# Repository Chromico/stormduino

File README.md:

# Stormduino Rev 2.2
An open source arduino uno clone designed in KiCad in collaboration with tecknologg and cyberstorm.mu .The board uses the CH340C as the USB to serial converter and an Atmega328p (DIP) as the microcontroller. The board design and schematic is open source so do whatever you wish with it :)

My website: https://tecknologg.website

Blog post: https://tecknologg.website/2020/02/02/stormduino-the-arduino-compatible-board-made-in-kicad/

# Front 

# Back

# Assembled board

# Features

# Documentation
You can get the official documentation for stormduino here: https://github.com/Chromico/stormduino/blob/master/documentation.pdf

# Certification
As from 2020 Stormduino has the open source hardware certfication to show you that Stormduino is truly open source hardware.

# Contact

Need to contact me ? Just send me an email at nathan@tecknologg.website or tecknologg@gmail.com

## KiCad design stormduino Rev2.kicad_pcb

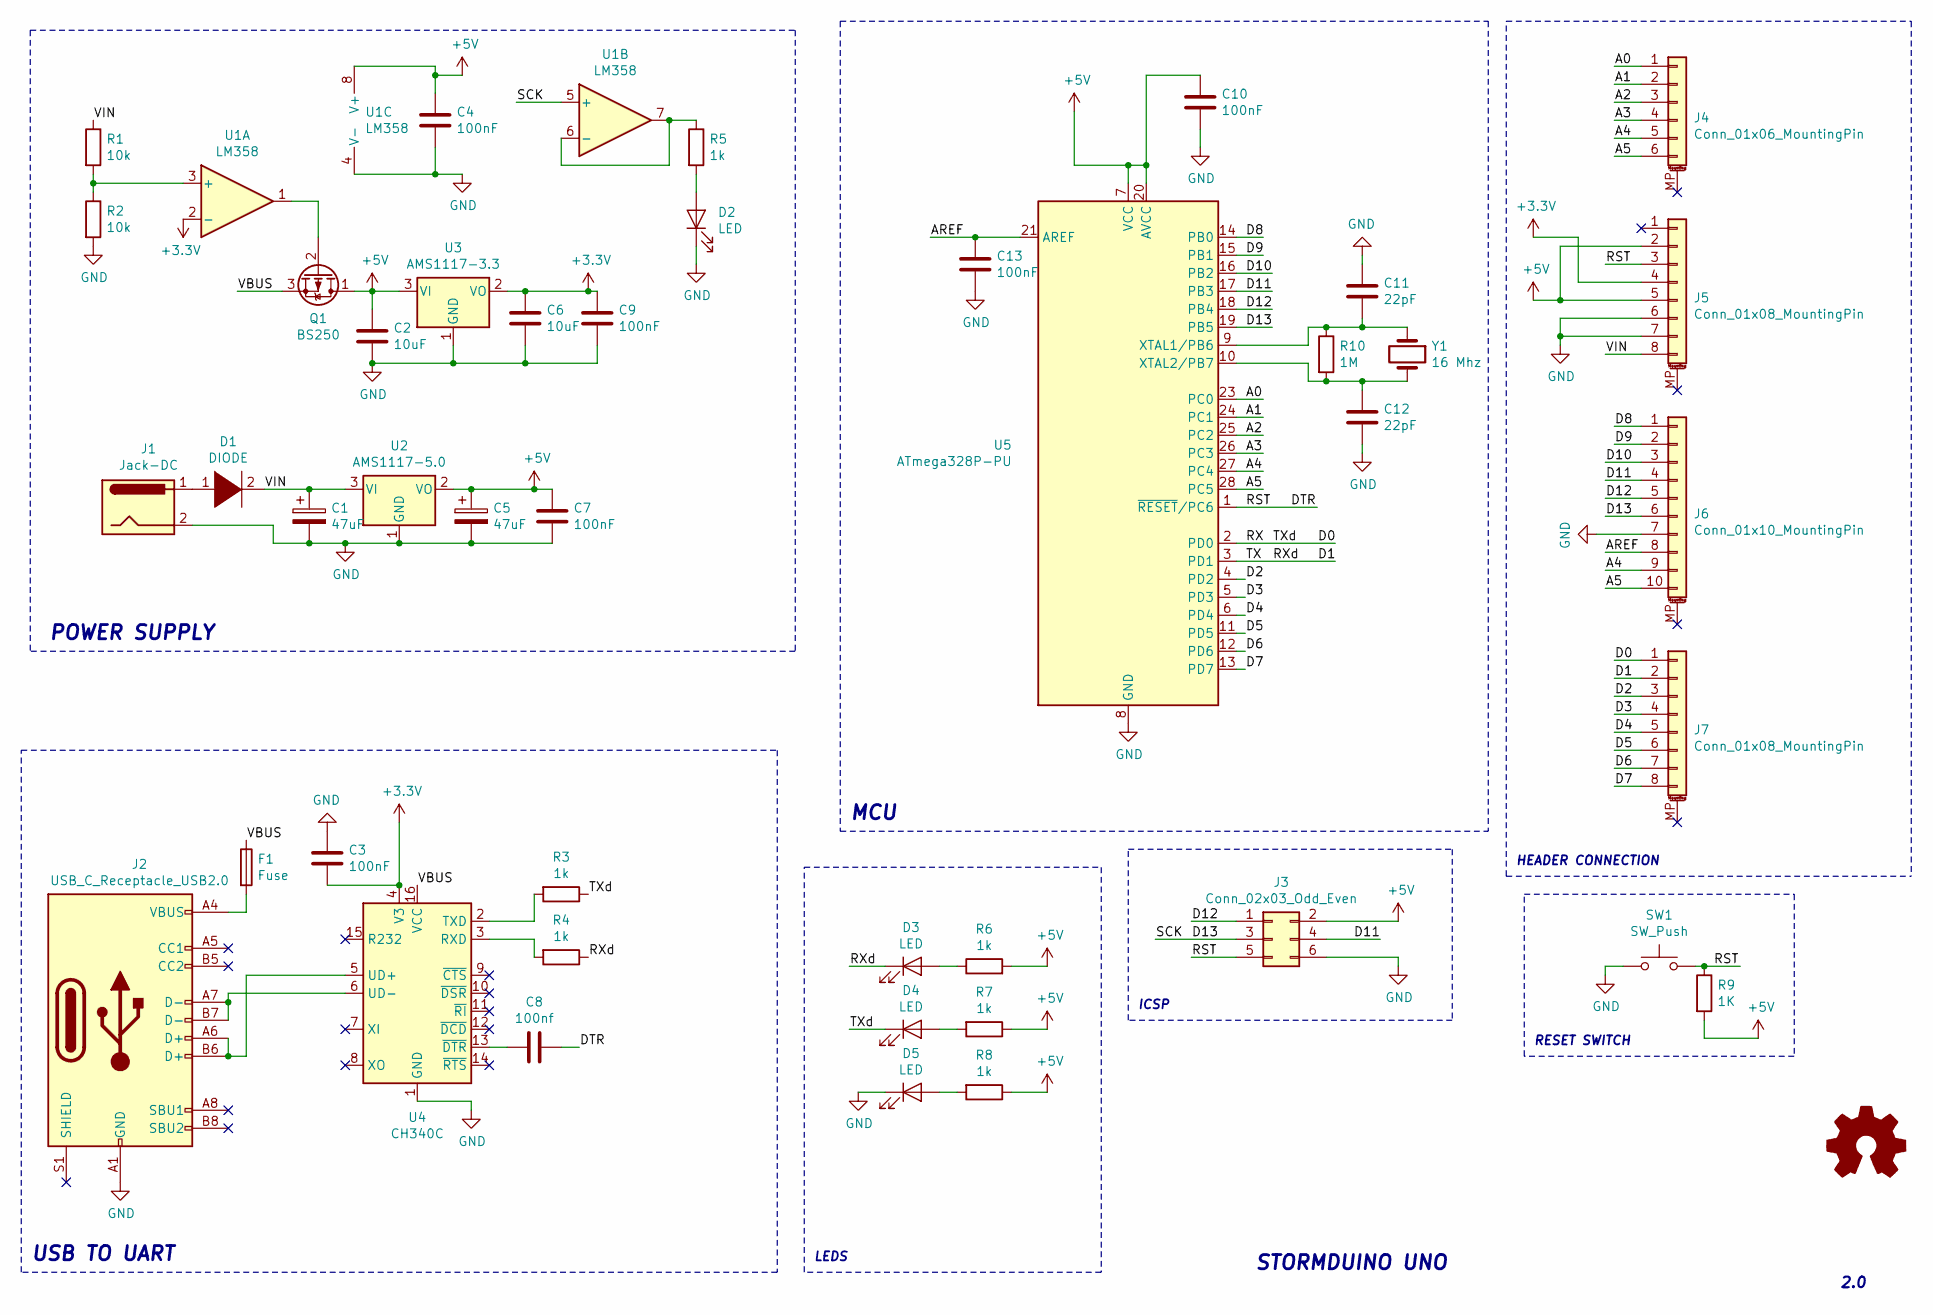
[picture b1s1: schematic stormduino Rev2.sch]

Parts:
C1, C5: 47uF
C2, C6: 10uF
C3, C4, C7, C9, C10, C13: 100nF
C8: 100nf
C11, C12: 22pF
D1: DIODE
D2, D3, D4, D5: LED
F1: Fuse
J1: Jack-DC
J2: USB_C_Receptacle_USB2.0
J3: Conn_02x03_Odd_Even
J4: Conn_01x06_MountingPin
J5, J7: Conn_01x08_MountingPin
J6: Conn_01x10_MountingPin
Q1: BS250; TO-92_Inline
R1, R2: 10k
R3, R4, R5, R6, R7, R8: 1k
R9: 1K
R10: 1M
SW1: SW_Push
U1: LM358
U2: AMS1117-5.0; SOT-223-3_TabPin2
U3: AMS1117-3.3; SOT-223-3_TabPin2
U4: CH340C; SOIC-16_3.9x9.9mm_P1.27mm
U5: ATmega328P-PU; DIP-28_W7.62mm
Y1: 16 Mhz

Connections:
+3V3: C3.2, C6.1, C9.1, J5.4, U1.2 (-), U3.2 (VO), U4.4 (V3)
/A0: J4.1, U5.23 (PC0)
/A1: J4.2, U5.24 (PC1)
/A2: J4.3, U5.25 (PC2)
/A3: J4.4, U5.26 (PC3)
/A4: J4.5, J6.9, U5.27 (PC4)
/A5: J4.6, J6.10, U5.28 (PC5)
/AREF: C13.1, J6.8, U5.21 (AREF)
/CTS: U4.9 (~CTS); also elsewhere on the board
/D0: D4.1 (K), J7.1, R3.1, U5.2 (PD0); also elsewhere on the board
/D1: D3.1 (K), J7.2, R4.1, U5.3 (PD1); also elsewhere on the board
/D2: J7.3, U5.4 (PD2)
/D3: J7.4, U5.5 (PD3)
/D4: J7.5, U5.6 (PD4)
/D5: J7.6, U5.11 (PD5)
/D6: J7.7, U5.12 (PD6)
/D7: J7.8, U5.13 (PD7)
/D8: J6.1, U5.14 (PB0)
/D9: J6.2, U5.15 (PB1)
/D10: J6.3, U5.16 (PB2)
/D11: J3.4, J6.4, U5.17 (PB3)
/D12: J3.1, J6.5, U5.18 (PB4)
/D13: J3.3, J6.6, U1.5 (+), U5.19 (PB5)
/DCD: U4.12 (~DCD); also elsewhere on the board
/DSR: U4.10 (~DSR); also elsewhere on the board
/DTR: C8.1, J3.5, J5.3, R9.1, SW1.2, U5.1 (~RESET~/PC6)
/R232: U4.15 (R232); also elsewhere on the board
/RI: U4.11 (~RI); also elsewhere on the board
/RTS: U4.14 (~RTS); also elsewhere on the board
/VBUS: F1.1, Q1.3 (S), U4.16 (VCC); also elsewhere on the board
/VIN: C1.1, D1.2 (A), J5.8, R1.1, U2.3 (VI)
GND: C1.2, C2.2, C3.1, C4.2, C5.2, C6.2, C7.2, C9.2, C10.2, C11.1, C12.2, C13.2, D2.1 (K), D5.1 (K), J1.2, J2.A1 (GND), J2.A12 (GND), J2.B1 (GND), J2.B12 (GND), J3.6, J5.6, J5.7, J6.7, R2.2, SW1.1, U1.4 (V-), U2.1 (GND), U3.1 (GND), U4.1 (GND), U5.8 (GND), U5.22 (GND); also elsewhere on the board
unnamed: C8.2, U4.13 (~DTR)
unnamed: C11.2, R10.1, U5.9 (XTAL1/PB6), Y1.1
unnamed: C12.1, R10.2, U5.10 (XTAL2/PB7), Y1.2
unnamed: D1.1 (K), J1.1
unnamed: D2.2 (A), R5.2
unnamed: D3.2 (A), R6.1
unnamed: D4.2 (A), R7.2
unnamed: D5.2 (A), R8.2
unnamed: F1.2, J2.A4 (VBUS), J2.A9 (VBUS), J2.B4 (VBUS), J2.B9 (VBUS)
unnamed: J2.A6 (D+), J2.B6 (D+), U4.5 (UD+)
unnamed: J2.A7 (D-), J2.B7 (D-), U4.6 (UD-)
unnamed: R1.2, R2.1, U1.3 (+)
unnamed: R3.2, U4.2 (TXD)
unnamed: R4.2, U4.3 (RXD)
unnamed: R5.1, U1.6 (-), U1.7

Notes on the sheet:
POWER SUPPLY
USB TO UART
MCU
STORMDUINO UNO
2.0
ICSP
HEADER CONNECTION
LEDS
RESET SWITCH

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
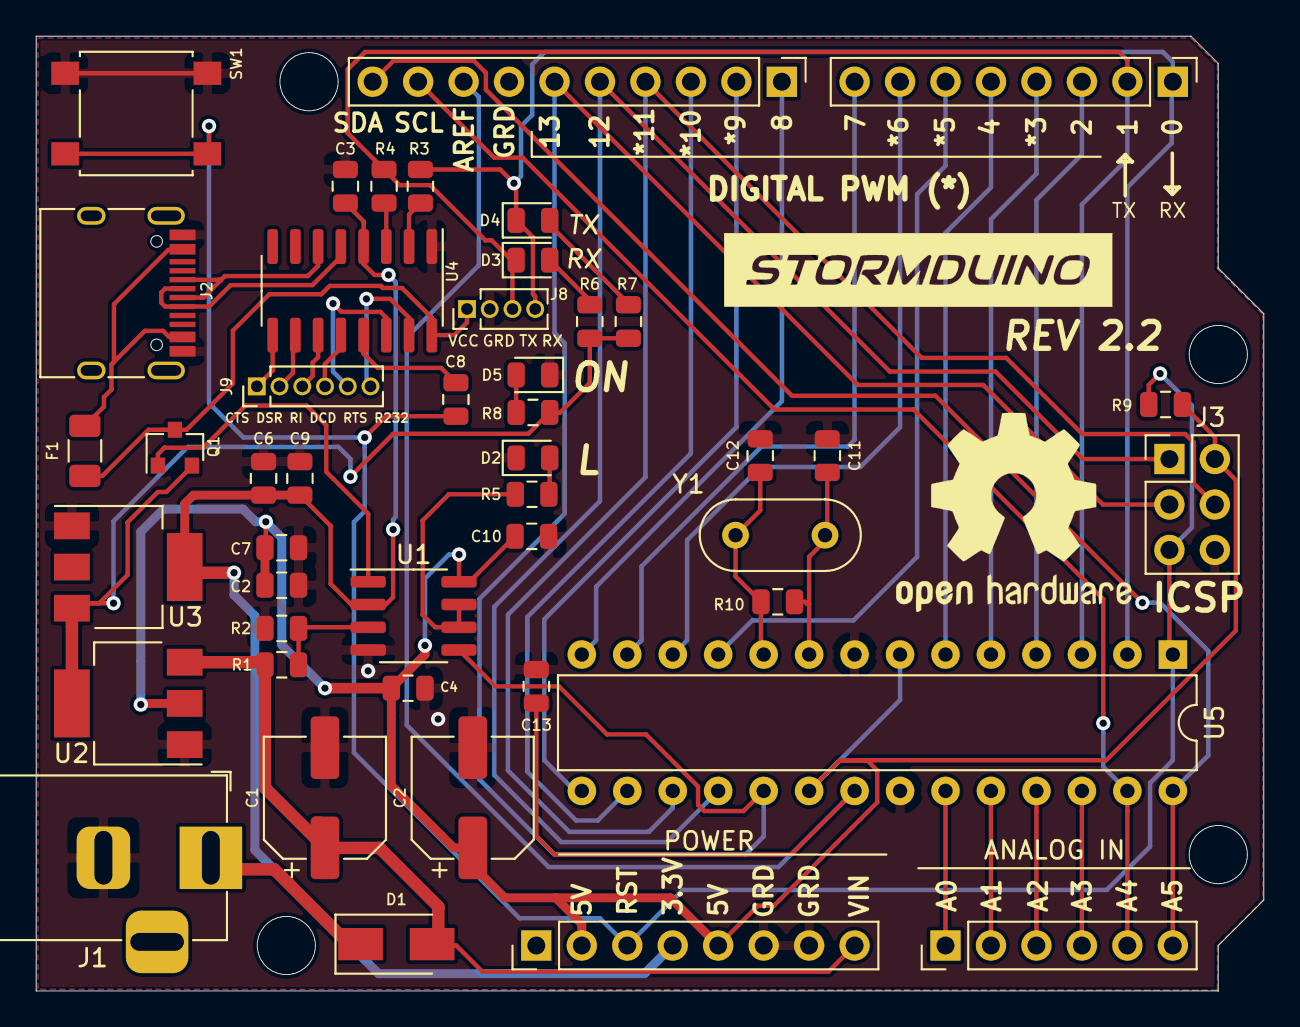
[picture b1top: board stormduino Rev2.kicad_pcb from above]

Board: 2 copper layers, 68.6 x 53.3 mm, 46 parts (0 on the bottom side), 49 nets.

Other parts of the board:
C2#2: 10uF; C_0805_2012Metric
J8: Conn_01x04_MountingPin; PinHeader_1x04_P1.27mm_Vertical
J9: Conn_01x06_MountingPin; PinHeader_1x06_P1.27mm_Vertical

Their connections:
/CTS: J9.1; also elsewhere on the board
/D0: J8.4; also elsewhere on the board
/D1: J8.3; also elsewhere on the board
/DCD: J9.4; also elsewhere on the board
/DSR: J9.2; also elsewhere on the board
/R232: J9.6; also elsewhere on the board
/RI: J9.3; also elsewhere on the board
/RTS: J9.5; also elsewhere on the board
/VBUS: J8.1; also elsewhere on the board
GND: C2#2.2, J8.2; also elsewhere on the board

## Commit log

2020-05-11 Create LICENSE
2020-06-07 [ImgBot] Optimize images
    /stormduino-features.png -- 318.57kb -> 277.59kb (12.86%)
